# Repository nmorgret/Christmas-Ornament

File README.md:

# Christmas-Ornament
**CR2032 powered, attiny controlled, Neopixel ornament**

Order boards [here](https://oshpark.com/shared_projects/MGq1ECv4 "https://oshpark.com/shared_projects/MGq1ECv4")

[PROGRAMMING-PORT](https://oshpark.com/shared_projects/NzWPFJYF "https://oshpark.com/shared_projects/NzWPFJYF") (reuseable)
[Github](https://github.com/nmorgret/Attiny-Port.git "https://github.com/nmorgret/Attiny-Port.git")

Partlist exported at 9/28/19 4:51 PM

|Part|Value           |Device          |Package                                               |Description                                  |   |
|----|----------------|----------------|------------------------------------------------------|---------------------------------------------|---|
|BT1 |3V              |BATTERY-20MM_SMD_4LEGS_OVERPASTE|BATTCON_20MM_4LEGS_OVERPASTE          |Battery - Single Cell                        |   |
|C1  |1uF             |C-USC0402       |C0402                                                 |CAPACITOR, American symbol                   |   |
|IC1 |ATTINY85-20SU   |ATTINY85-20SU   |SOT127P798X216-8N     |MICROCHIP - ATTINY85-20SU - MICROCONTROLLER MCU, 8 BIT, ATTINY, 20MHZ, SOIC-8|   |
|R1  |10k             |R-US_R0402      |R0402                                                 |RESISTOR, American symbol                    |   |
|S1  |MOMENTARY-SWITCH-SPST-PTH-6.0MM|MOMENTARY-SWITCH-SPST-PTH-6.0MM|TACTILE_SWITCH_PTH_6.0MM|Momentary Switch (Pushbutton) - SPST         |   |
|U$1 |SK6812          |SK6812          |OSCL320P500X500X160-4N                                |                                             |   |
|U$2 |SK6812          |SK6812          |OSCL320P500X500X160-4N                                |                                             |   |
|U$3 |SK6812          |SK6812          |OSCL320P500X500X160-4N                                |                                             |   |
|U$4 |SK6812          |SK6812          |OSCL320P500X500X160-4N                                |                                             |   |
|U$5 |PROGRAMMING-PORT|PROGRAMMING-PORT|PROGRAMMING-PORT                                      |                                             |   |
|U$6 |SLIDE-SWITCH    |SLIDE-SWITCH    |SLIDE-SWITCH                                          |                                             |   |

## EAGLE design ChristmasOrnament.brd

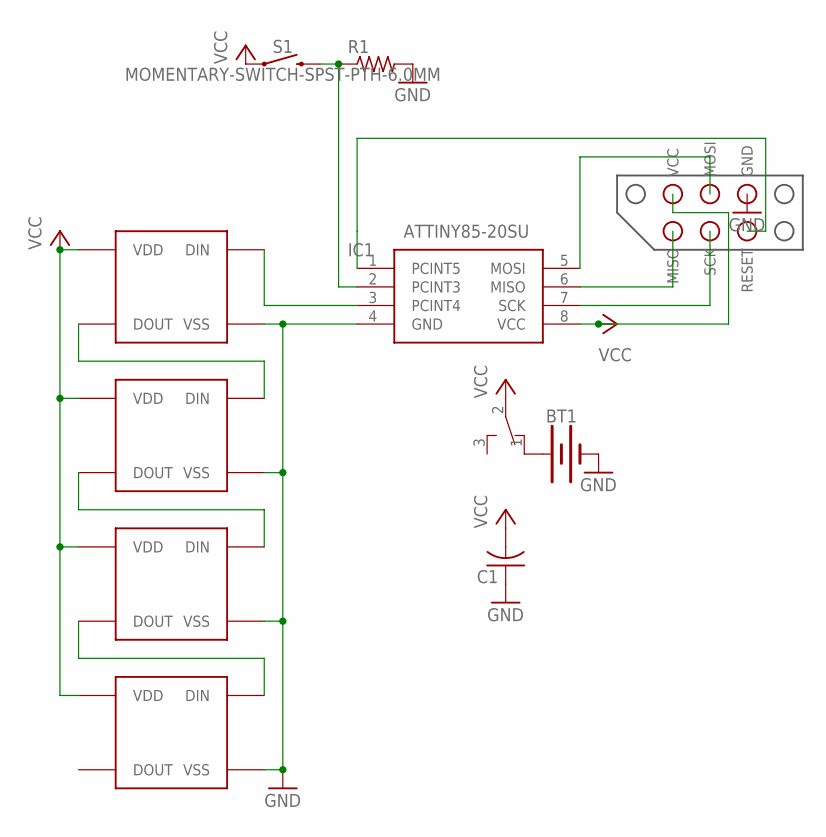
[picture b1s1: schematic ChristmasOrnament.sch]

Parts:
BT1: BATTERY-20MM_SMD_4LEGS_OVERPASTE; BATTCON_20MM_4LEGS_OVERPASTE
C1: C-USC0402; C0402
IC1: ATTINY85-20SU; SOT127P798X216-8N
R1: R-US_R0402; R0402
S1: MOMENTARY-SWITCH-SPST-PTH-6.0MM; TACTILE_SWITCH_PTH_6.0MM
U$1, U$2, U$3, U$4: SK6812; OSCL320P500X500X160-4N
U$5: PROGRAMMING-PORT
U$6: SLIDE-SWITCH

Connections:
GND: BT1.2 (-), C1.1, IC1.4 (GND), R1.2, U$1.3 (VSS), U$2.3 (VSS), U$3.3 (VSS), U$4.3 (VSS), U$5.P$6 (GND)
unnamed: U$1.2 (DOUT), U$2.4 (DIN)
unnamed: U$2.2 (DOUT), U$3.4 (DIN)
unnamed: U$3.2 (DOUT), U$4.4 (DIN)
unnamed: IC1.1 (PCINT5), U$5.P$5 (RESET)
unnamed: IC1.7 (SCK), U$5.P$3 (SCK)
unnamed: IC1.3 (PCINT4), U$1.4 (DIN)
unnamed: IC1.6 (MISO), U$5.P$1 (MISO)
unnamed: IC1.5 (MOSI), U$5.P$4 (MOSI)
unnamed: IC1.2 (PCINT3), R1.1, S1.3 (2)
unnamed: BT1.1 (+), U$6.1
VCC: C1.2, IC1.8 (VCC), S1.1, U$1.1 (VDD), U$2.1 (VDD), U$3.1 (VDD), U$4.1 (VDD), U$5.P$2 (VCC), U$6.2

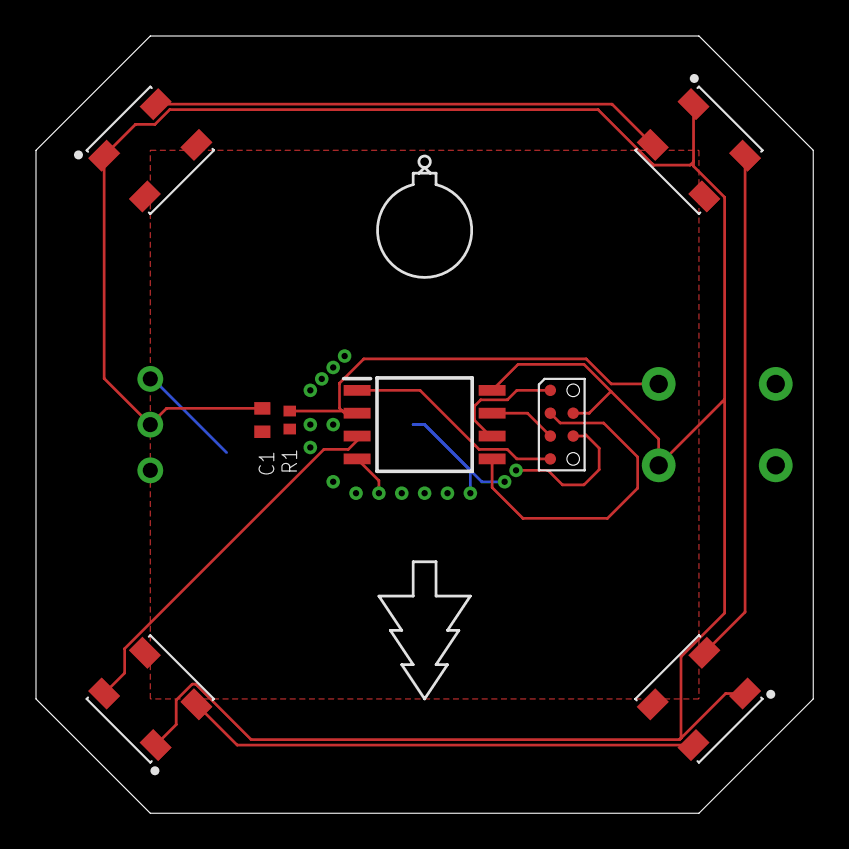
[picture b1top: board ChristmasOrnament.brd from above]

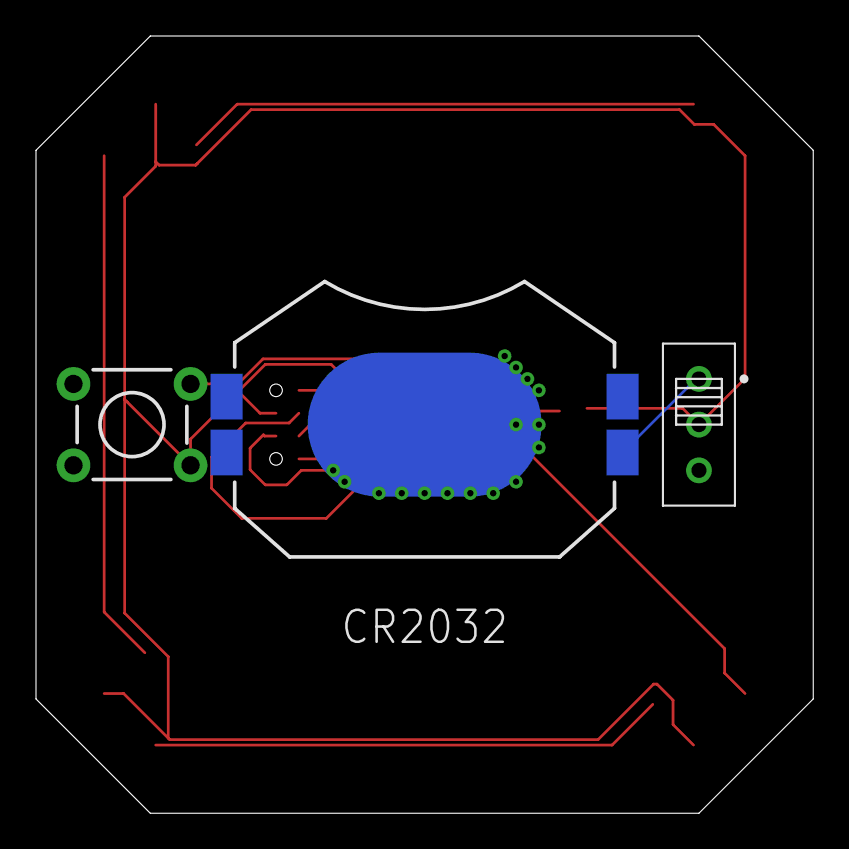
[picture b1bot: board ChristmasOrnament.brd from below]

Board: 2 copper layers, 43.2 x 43.2 mm, 11 parts (3 on the bottom side), 12 nets.

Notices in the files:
parts and their libraries:
SparkFun-Batteries: Licensing: Creative Commons ShareAlike 4.0 International - https://creativecommons.org/licenses/by-sa/4.0
